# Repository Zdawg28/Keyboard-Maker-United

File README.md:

View this project on [CADLAB.io](https://cadlab.io/project/30098). 

# Keyboard-Maker-United
IEEE Mechanical Keyboard Project Team at Cal Poly Pomona

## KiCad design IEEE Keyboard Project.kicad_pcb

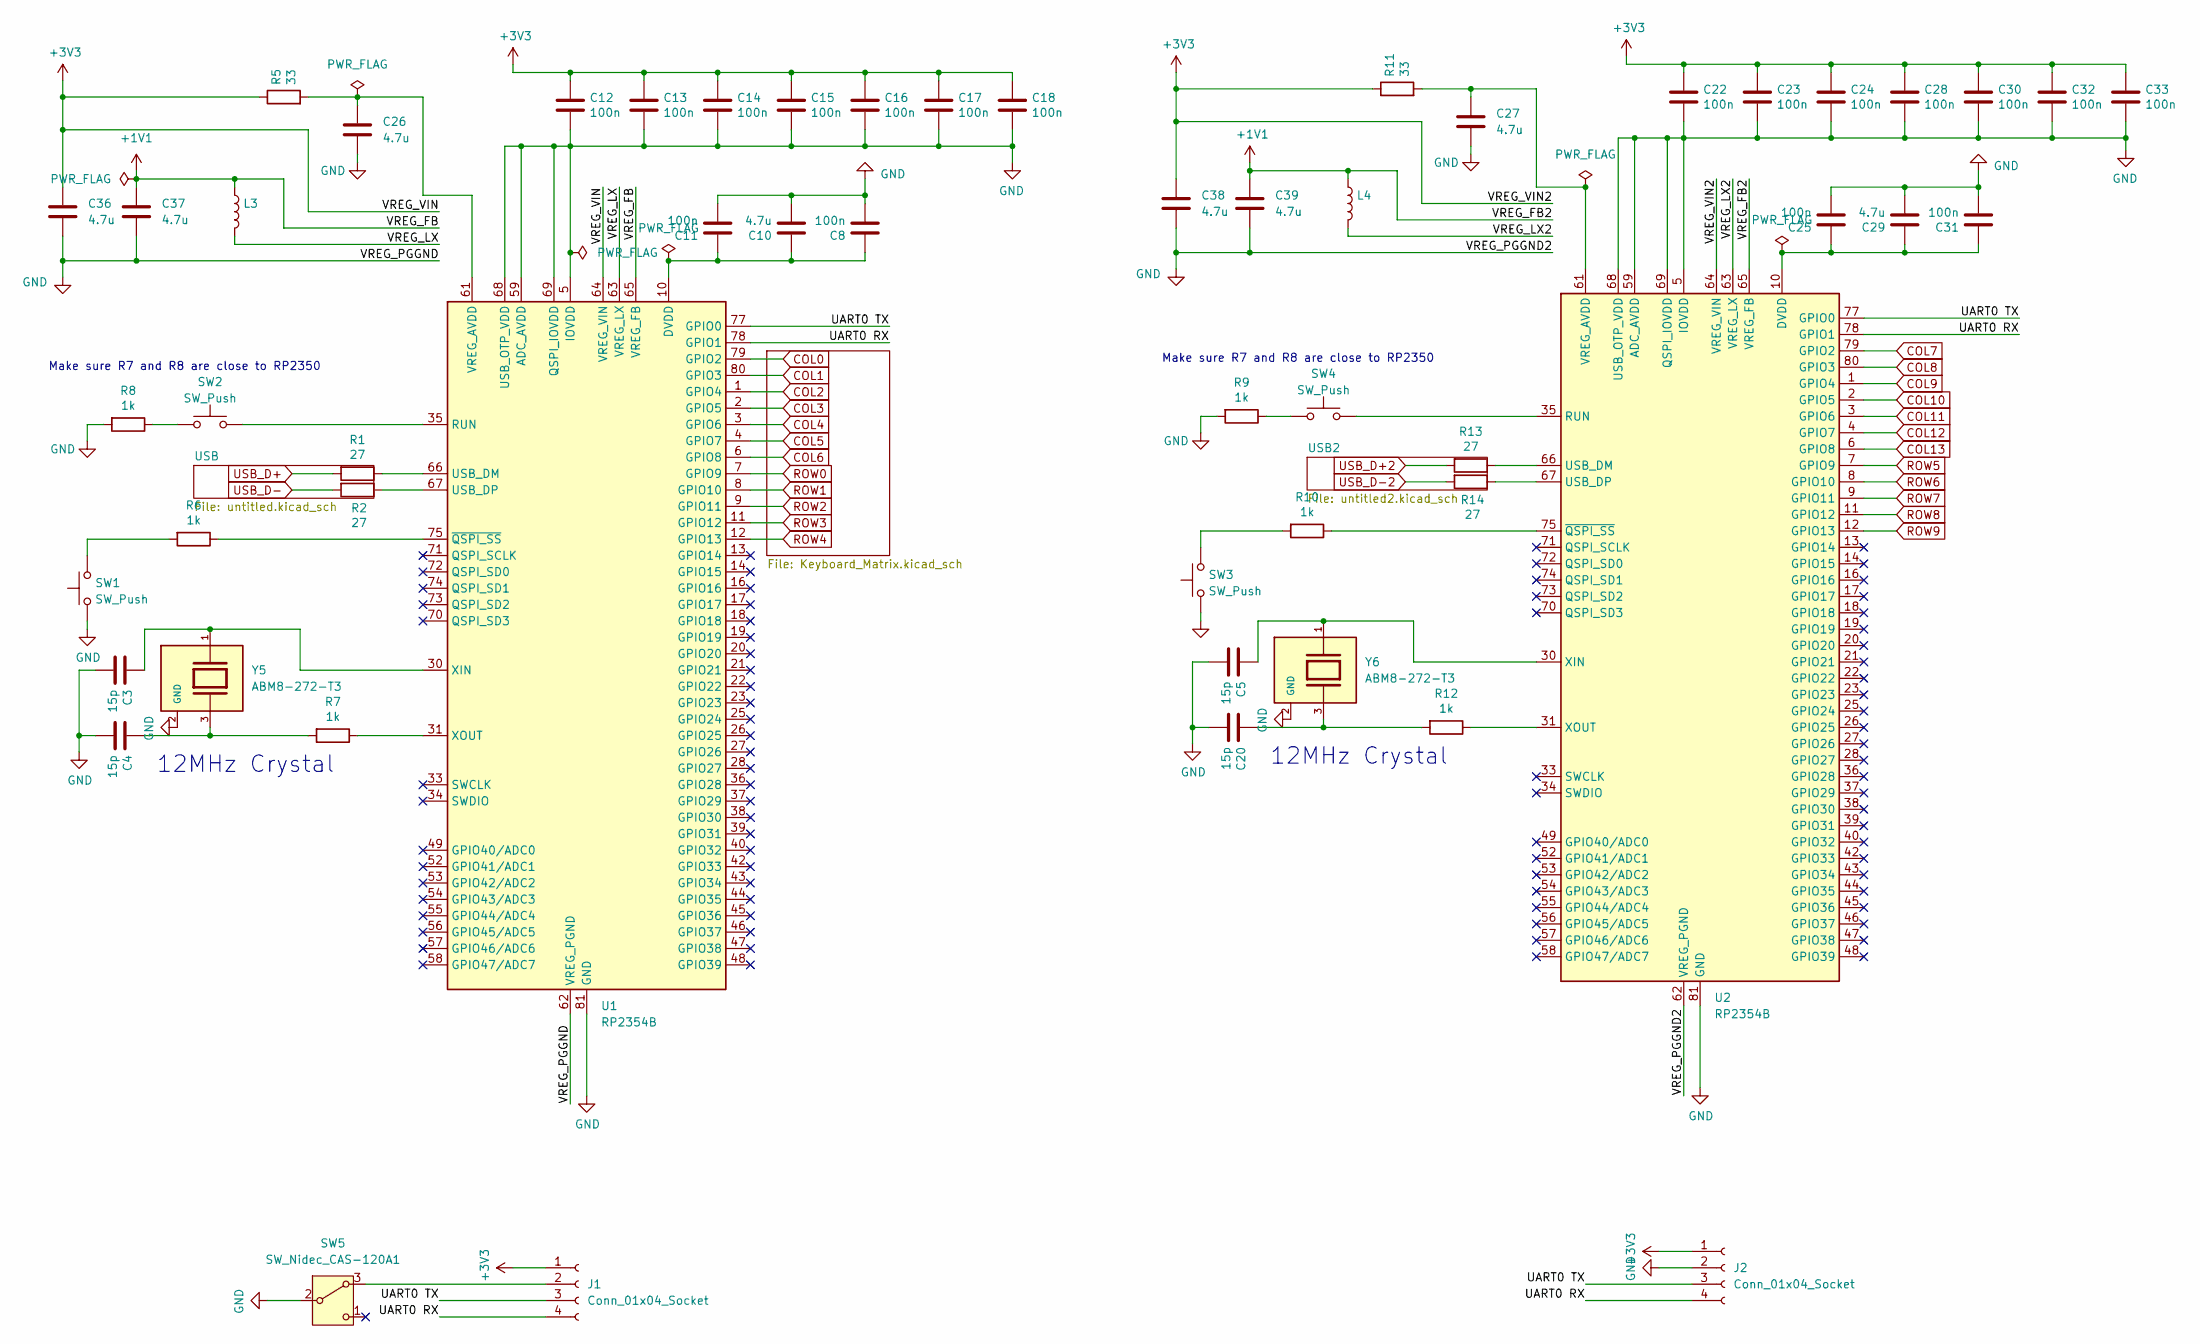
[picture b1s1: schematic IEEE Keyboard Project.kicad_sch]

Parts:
C3, C4, C5, C20: 15p; C_0402_1005Metric
C8, C11, C12, C13, C14, C15, C16, C17, C18, C22, C23, C24, C25, C28, C30, C31, C32, C33: 100n; C_0402_1005Metric
C10, C26, C27, C29, C36, C37, C38, C39: 4.7u; C_0402_1005Metric
J1, J2: Conn_01x04_Socket; JST_EH_S4B-EH_1x04_P2.50mm_Horizontal
L3, L4: 3.3u; L_Coilcraft_LPS3314
R1, R2, R13, R14: 27; R_0402_1005Metric
R5, R11: 33; R_0402_1005Metric
R6, R7, R8, R9, R10, R12: 1k; R_0402_1005Metric
SW1, SW2, SW3, SW4: SW_Push; SW_Push_1P1T_NO_Vertical_Wuerth_434133025816
SW5: SW_Nidec_CAS-120A1; Nidec_Copal_CAS-120A
U1, U2: RP2354B; QFN-80-1EP_10x10mm_P0.4mm_EP3.4x3.4mm
Y5, Y6: ABM8-272-T3; XTAL_ABM8-272-T3; PARTREV 07-29-20

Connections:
+1V1: C37.1, C39.1, L3.1, L4.1, U1.65 (VREG_FB), U2.65 (VREG_FB)
/UART0 RX: J1.4, J2.4, U1.78 (GPIO1), U2.78 (GPIO1)
/UART0 TX: J1.3, J2.3, U1.77 (GPIO0), U2.77 (GPIO0)
/VREG_LX: L3.2, U1.63 (VREG_LX)
/VREG_LX2: L4.2, U2.63 (VREG_LX)
COL0: U1.79 (GPIO2); also elsewhere on the board
COL1: U1.80 (GPIO3); also elsewhere on the board
COL2: U1.1 (GPIO4); also elsewhere on the board
COL3: U1.2 (GPIO5); also elsewhere on the board
COL4: U1.3 (GPIO6); also elsewhere on the board
COL5: U1.4 (GPIO7); also elsewhere on the board
COL6: U1.6 (GPIO8); also elsewhere on the board
COL7: U2.79 (GPIO2); also elsewhere on the board
COL8: U2.80 (GPIO3); also elsewhere on the board
COL12: U2.4 (GPIO7); also elsewhere on the board
COL13: U2.6 (GPIO8); also elsewhere on the board
unnamed: C4.1, R7.2, Y5.3
unnamed: C8.1, C10.1, C11.1, U1.10 (DVDD), U1.32 (DVDD), U1.51 (DVDD)
unnamed 18: C20.1, R12.2, Y6.3; also elsewhere on the board
unnamed: C25.1, C29.1, C31.1, U2.10 (DVDD), U2.32 (DVDD), U2.51 (DVDD)
unnamed: J1.2, SW5.3 (A)
unnamed: R6.2, SW1.2
unnamed: R8.1, SW2.1
unnamed: R9.1, SW4.1
unnamed: R10.2, SW3.2
unnamed: SW2.2, U1.35 (RUN)
unnamed: R1.1, U1.66 (USB_DM)
unnamed: R2.1, U1.67 (USB_DP)
unnamed: C26.1, R5.2, U1.61 (VREG_AVDD)
unnamed: C3.1, U1.30 (XIN), Y5.1
unnamed: R7.1, U1.31 (XOUT)
unnamed: R6.1, U1.75 (~QSPI_SS)
unnamed: SW4.2, U2.35 (RUN)
unnamed: R13.1, U2.66 (USB_DM)
unnamed: R14.1, U2.67 (USB_DP)
unnamed: C27.1, R11.2, U2.61 (VREG_AVDD)
unnamed 97: R12.1, U2.31 (XOUT); also elsewhere on the board
unnamed: R10.1, U2.75 (~QSPI_SS)
ROW0: U1.7 (GPIO9); also elsewhere on the board
ROW1: U1.8 (GPIO10); also elsewhere on the board
ROW2: U1.9 (GPIO11); also elsewhere on the board
ROW3: U1.11 (GPIO12); also elsewhere on the board
ROW4: U1.12 (GPIO13); also elsewhere on the board
ROW5: U2.7 (GPIO9); also elsewhere on the board
ROW6: U2.8 (GPIO10); also elsewhere on the board
ROW7: U2.9 (GPIO11); also elsewhere on the board
ROW8: U2.11 (GPIO12); also elsewhere on the board
ROW9: U2.12 (GPIO13); also elsewhere on the board
USB_D+: R1.2; also elsewhere on the board
USB_D+2: R13.2; also elsewhere on the board
USB_D-: R2.2; also elsewhere on the board
USB_D-2: R14.2; also elsewhere on the board

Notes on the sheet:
Make sure R7 and R8 are close to RP2350
12MHz Crystal

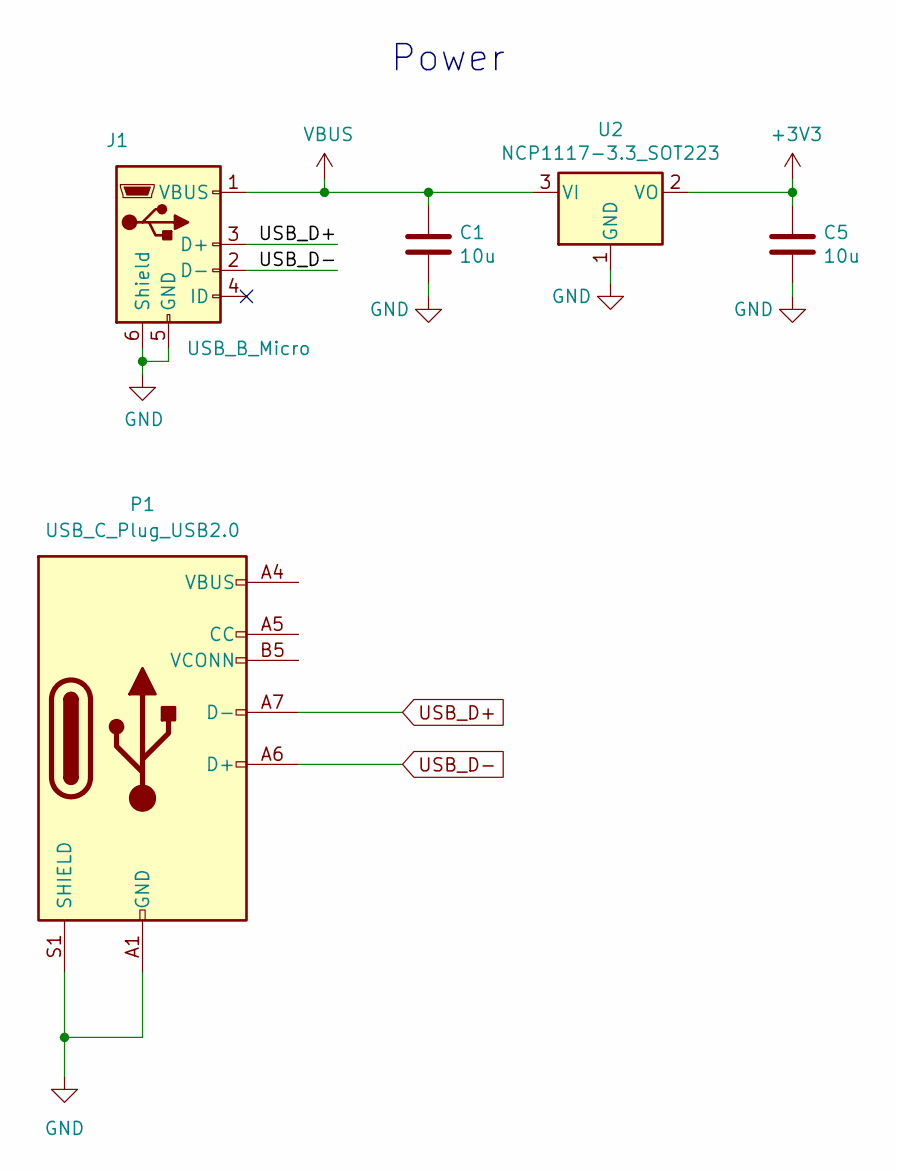
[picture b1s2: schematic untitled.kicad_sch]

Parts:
C1, C5: 10u; C_0805_2012Metric
J1: USB_B_Micro; USB_Micro-B_Amphenol_10103594-0001LF_Horizontal
P1: USB_C_Plug_USB2.0
U2: NCP1117-3.3_SOT223; SOT-223-3_TabPin2

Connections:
/UART0 RX: J1.4; also elsewhere on the board
/UART0 TX: J1.3; also elsewhere on the board
unnamed 76: J1.2; also elsewhere on the board
unnamed: P1.A4 (VBUS), P1.A9 (VBUS), P1.B4 (VBUS), P1.B9 (VBUS)

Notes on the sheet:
Power

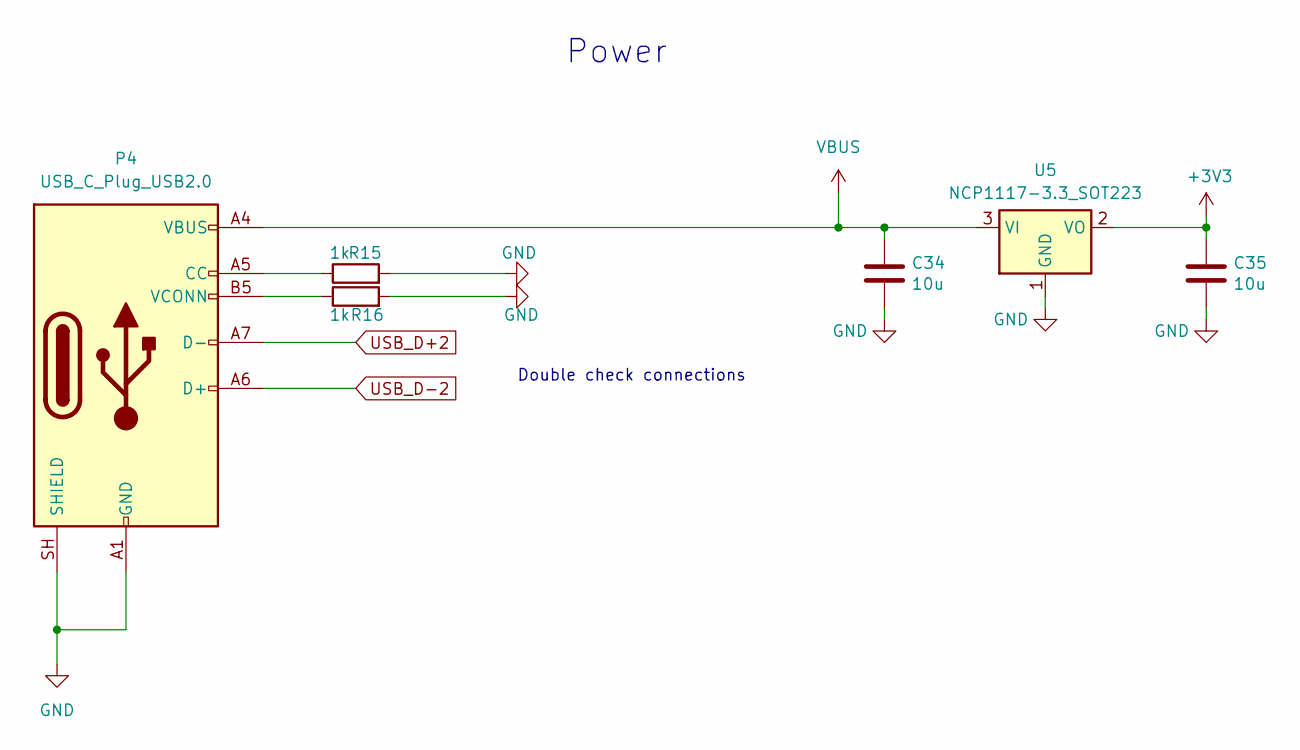
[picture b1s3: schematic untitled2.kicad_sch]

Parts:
C34, C35: 10u; C_0805_2012Metric
P4: USB_C_Plug_USB2.0
R15, R16: 1k; R_0402_1005Metric
U5: NCP1117-3.3_SOT223; SOT-223-3_TabPin2

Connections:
unnamed: P4.A5 (CC), R15.1
unnamed: P4.B5 (VCONN), R16.1
USB_D+2: P4.A7 (D-); also elsewhere on the board
USB_D-2: P4.A6 (D+); also elsewhere on the board
VBUS: C34.1, P4.A4 (VBUS), P4.A9 (VBUS), P4.B4 (VBUS), P4.B9 (VBUS), U5.3 (VI); also elsewhere on the board

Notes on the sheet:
Double check connections
Power

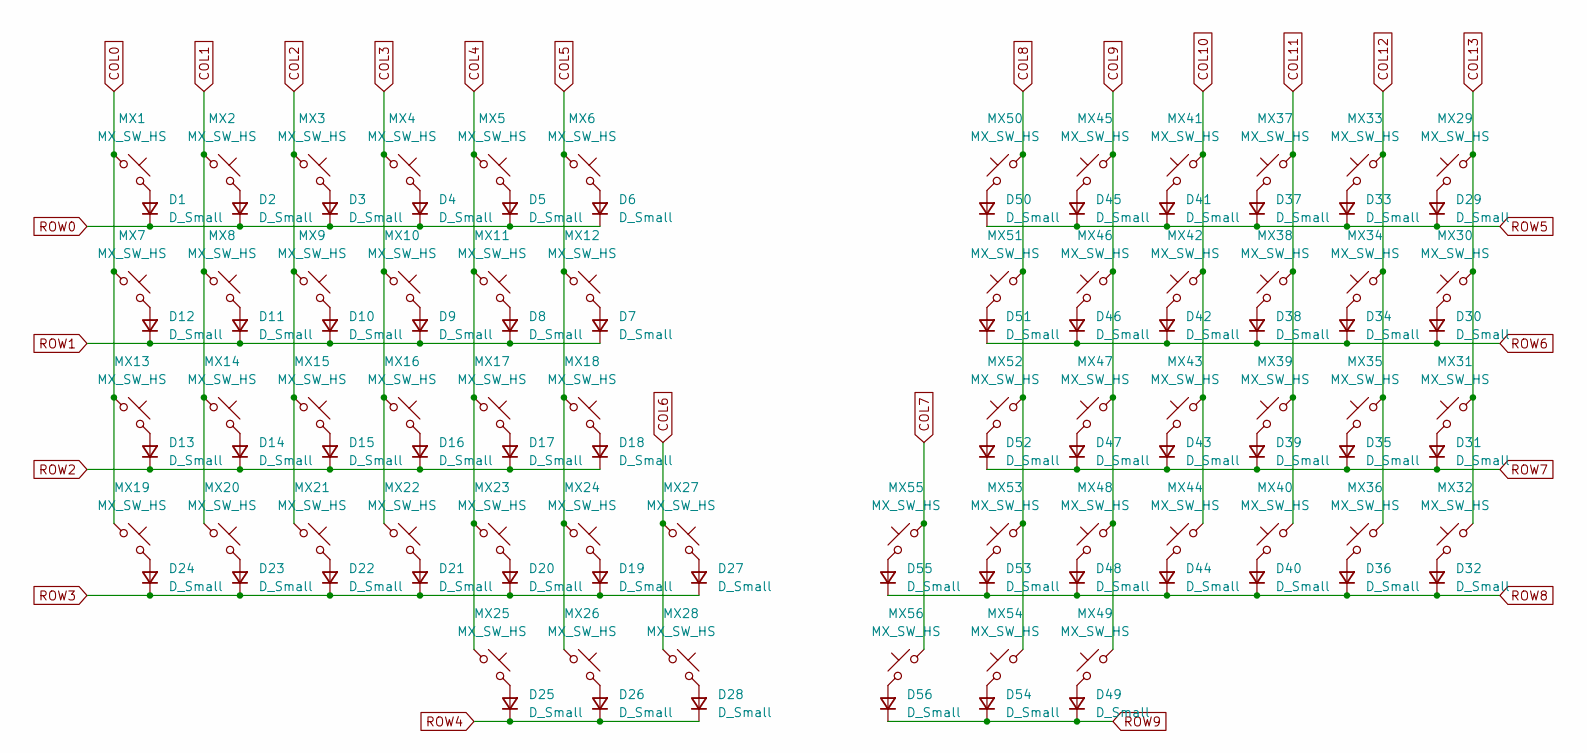
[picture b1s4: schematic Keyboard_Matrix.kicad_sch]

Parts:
D1, D2, D3, D4, D5, D6, D7, D8, D9, D10, D11, D12, D13, D14, D15, D16, D17, D18, D19, D20, D21, D22, D23, D24, D25, D26, D27, D28, D29, D30, D31, D32, D33, D34, D35, D36, D37, D38, D39, D40, D41, D42, D43, D44, D45, D46, D47, D48, D49, D50, D51, D52, D53, D54, D55, D56: D_Small; D_01005_0402Metric
MX1, MX2, MX3, MX4, MX5, MX6, MX7, MX8, MX9, MX10, MX11, MX12, MX13, MX14, MX15, MX16, MX17, MX18, MX19, MX20, MX21, MX22, MX23, MX24, MX25, MX26, MX27, MX28, MX29, MX30, MX31, MX32, MX33, MX34, MX35, MX36, MX37, MX38, MX39, MX40, MX41, MX42, MX43, MX44, MX45, MX46, MX47, MX48, MX49, MX50, MX51, MX52, MX53, MX54, MX55, MX56: MX_SW_HS; SW_Cherry_MX_1.00u_PCB

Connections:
COL0: MX1.1, MX7.1, MX13.1, MX19.1; also elsewhere on the board
COL1: MX2.1, MX8.1, MX14.1, MX20.1; also elsewhere on the board
COL2: MX3.1, MX9.1, MX15.1, MX21.1; also elsewhere on the board
COL3: MX4.1, MX10.1, MX16.1, MX22.1; also elsewhere on the board
COL4: MX5.1, MX11.1, MX17.1, MX23.1, MX25.1; also elsewhere on the board
COL5: MX6.1, MX12.1, MX18.1, MX24.1, MX26.1; also elsewhere on the board
COL6: MX27.1, MX28.1; also elsewhere on the board
COL7: MX55.1, MX56.1; also elsewhere on the board
COL8: MX50.1, MX51.1, MX52.1, MX53.1, MX54.1; also elsewhere on the board
COL12: MX33.1, MX34.1, MX35.1, MX36.1; also elsewhere on the board
COL13: MX29.1, MX30.1, MX31.1, MX32.1; also elsewhere on the board
unnamed: D1.2 (A), MX1.2
unnamed: D2.2 (A), MX2.2
unnamed: D3.2 (A), MX3.2
unnamed: D4.2 (A), MX4.2
unnamed: D5.2 (A), MX5.2
unnamed: D6.2 (A), MX6.2
unnamed: D7.2 (A), MX12.2
unnamed: D8.2 (A), MX11.2
unnamed: D9.2 (A), MX10.2
unnamed: D10.2 (A), MX9.2
unnamed: D11.2 (A), MX8.2
unnamed: D12.2 (A), MX7.2
unnamed: D13.2 (A), MX13.2
unnamed: D14.2 (A), MX14.2
unnamed: D15.2 (A), MX15.2
unnamed: D16.2 (A), MX16.2
unnamed: D17.2 (A), MX17.2
unnamed: D18.2 (A), MX18.2
unnamed: D19.2 (A), MX24.2
unnamed: D20.2 (A), MX23.2
unnamed: D21.2 (A), MX22.2
unnamed: D22.2 (A), MX21.2
unnamed: D23.2 (A), MX20.2
unnamed: D24.2 (A), MX19.2
unnamed: D25.2 (A), MX25.2
unnamed: D26.2 (A), MX26.2
unnamed: D27.2 (A), MX27.2
unnamed: D28.2 (A), MX28.2
unnamed: D29.2 (A), MX29.2
unnamed: D30.2 (A), MX30.2
unnamed: D31.2 (A), MX31.2
unnamed: D32.2 (A), MX32.2
unnamed: D33.2 (A), MX33.2
unnamed: D34.2 (A), MX34.2
unnamed: D35.2 (A), MX35.2
unnamed: D36.2 (A), MX36.2
unnamed: D37.2 (A), MX37.2
unnamed: D38.2 (A), MX38.2
unnamed: D39.2 (A), MX39.2
unnamed: D40.2 (A), MX40.2
unnamed: D41.2 (A), MX41.2
unnamed: D42.2 (A), MX42.2
unnamed: D43.2 (A), MX43.2
unnamed: D44.2 (A), MX44.2
unnamed: D45.2 (A), MX45.2
unnamed: D46.2 (A), MX46.2
unnamed: D47.2 (A), MX47.2
unnamed: D48.2 (A), MX48.2
unnamed: D49.2 (A), MX49.2
unnamed: D50.2 (A), MX50.2
unnamed: D51.2 (A), MX51.2
unnamed: D52.2 (A), MX52.2
unnamed: D53.2 (A), MX53.2
unnamed: D54.2 (A), MX54.2
unnamed: D55.2 (A), MX55.2
unnamed: D56.2 (A), MX56.2
ROW0: D1.1 (K), D2.1 (K), D3.1 (K), D4.1 (K), D5.1 (K), D6.1 (K); also elsewhere on the board
ROW1: D7.1 (K), D8.1 (K), D9.1 (K), D10.1 (K), D11.1 (K), D12.1 (K); also elsewhere on the board
ROW2: D13.1 (K), D14.1 (K), D15.1 (K), D16.1 (K), D17.1 (K), D18.1 (K); also elsewhere on the board
ROW3: D19.1 (K), D20.1 (K), D21.1 (K), D22.1 (K), D23.1 (K), D24.1 (K), D27.1 (K); also elsewhere on the board
ROW4: D25.1 (K), D26.1 (K), D28.1 (K); also elsewhere on the board
ROW5: D29.1 (K), D33.1 (K), D37.1 (K), D41.1 (K), D45.1 (K), D50.1 (K); also elsewhere on the board
ROW6: D30.1 (K), D34.1 (K), D38.1 (K), D42.1 (K), D46.1 (K), D51.1 (K); also elsewhere on the board
ROW7: D31.1 (K), D35.1 (K), D39.1 (K), D43.1 (K), D47.1 (K), D52.1 (K); also elsewhere on the board
ROW8: D32.1 (K), D36.1 (K), D40.1 (K), D44.1 (K), D48.1 (K), D53.1 (K), D55.1 (K); also elsewhere on the board
ROW9: D49.1 (K), D54.1 (K), D56.1 (K); also elsewhere on the board

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
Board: 4 copper layers, 183 parts (55 on the bottom side), 119 nets, no tracks yet.

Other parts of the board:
C2, C6: 10u; C_0805_2012Metric
C5#2, C20#2: 15p; C_0402_1005Metric
P3: USB_C_Plug_USB2.0; TE_2340901-1
R3, R4, R12#2: 1k; R_0402_1005Metric
U4: NCP1117-3.3_SOT223; SOT-223-3_TabPin2
Y2: ABM8-272-T3; Crystal_SMD_3225-4Pin_3.2x2.5mm

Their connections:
unnamed 18: C20#2.1, R12#2.2, Y2.3; also elsewhere on the board
unnamed: P3.A5 (CC), R3.1
unnamed: P3.B5 (VCONN), R4.1
unnamed 97: R12#2.1; also elsewhere on the board
USB_D+: P3.A7 (D-); also elsewhere on the board
USB_D-: P3.A6 (D+); also elsewhere on the board
VBUS: C2.1, U4.3 (VI); also elsewhere on the board

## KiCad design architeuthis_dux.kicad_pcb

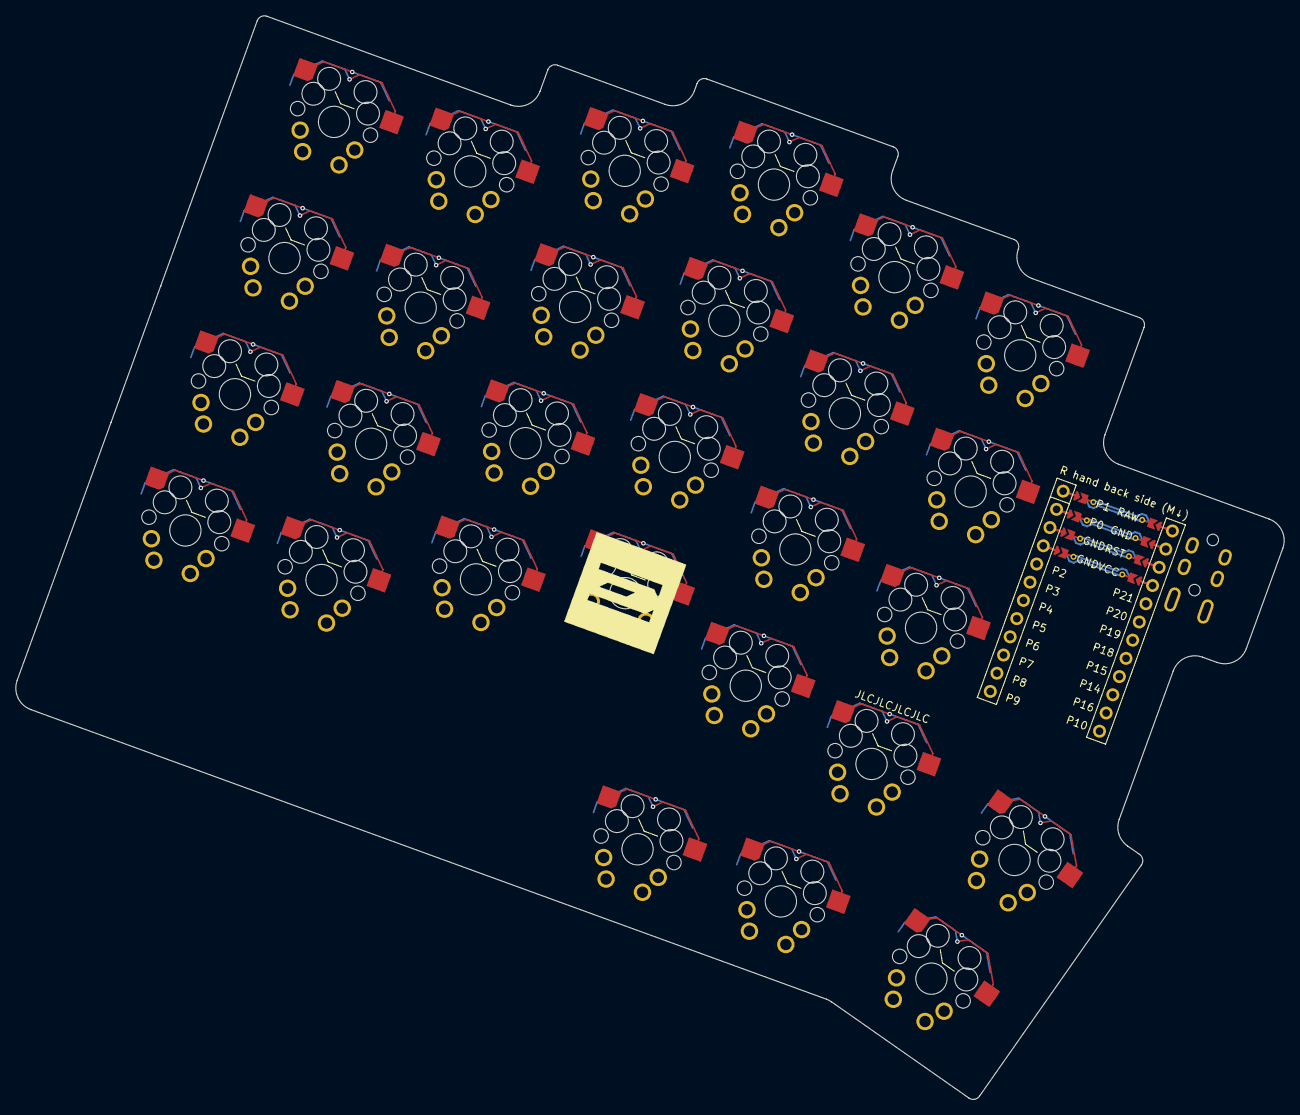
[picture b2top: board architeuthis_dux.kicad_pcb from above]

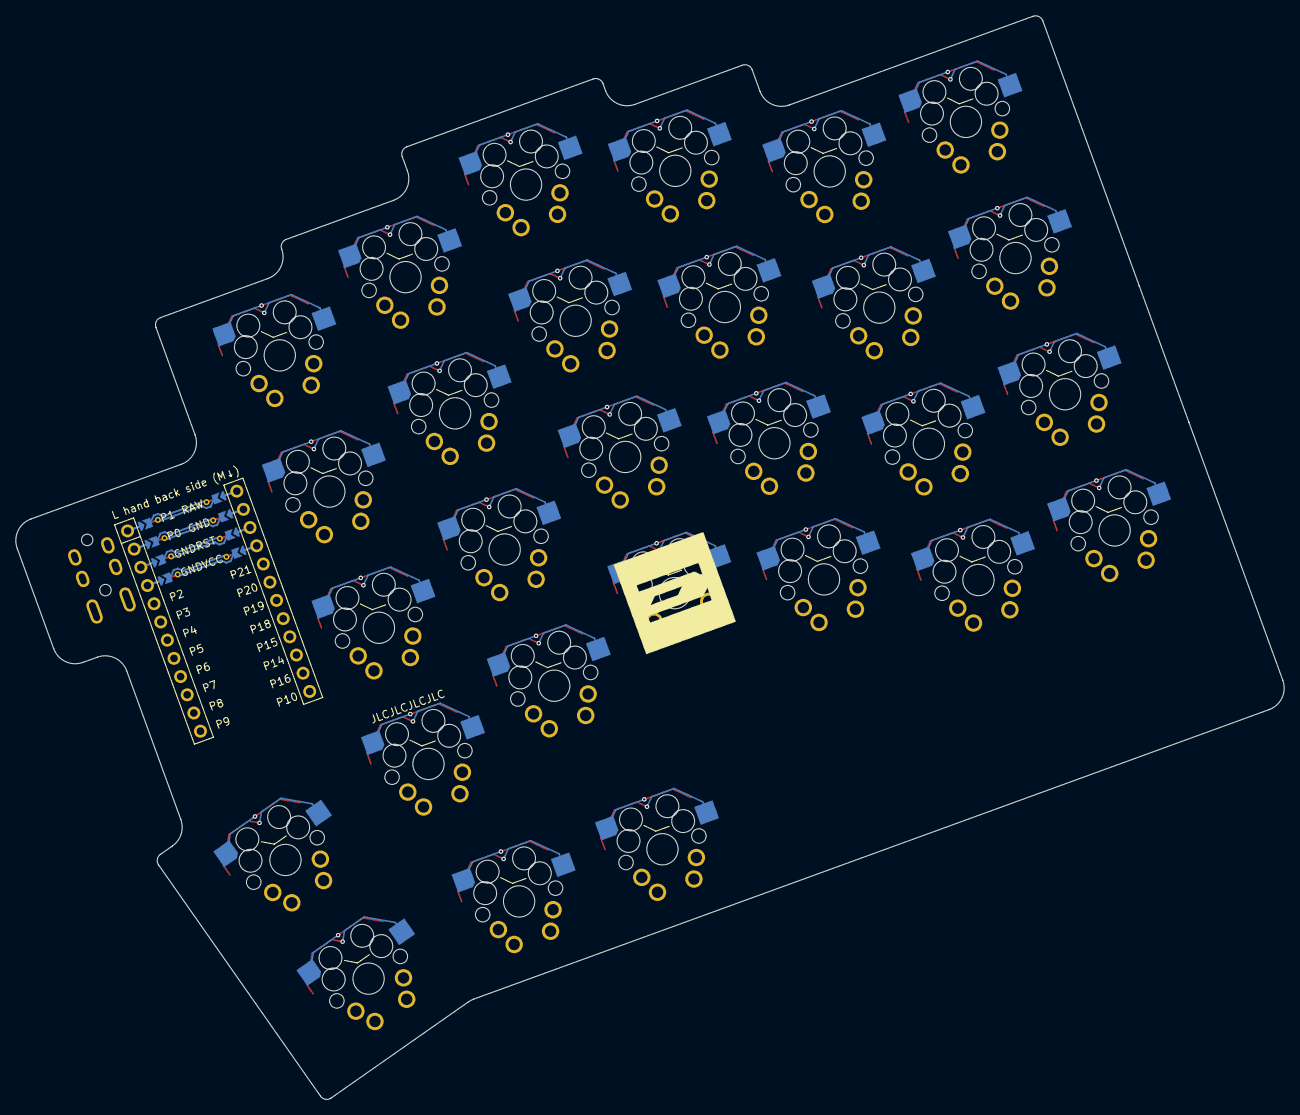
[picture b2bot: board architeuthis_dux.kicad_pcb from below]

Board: 2 copper layers, 166.3 x 142.1 mm, 31 parts (28 on the bottom side), 4 nets.

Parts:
LOGO1: utility_ergogen_logo
MCU1: mcu_nice_nano
S1, S2, S3, S4, S5, S6, S7, S8, S9, S10, S11, S12, S13, S14, S15, S16, S17, S18, S19, S20, S21, S22, S23, S24, S25, S26, S27, S28: switch_mx
TRRS1: trrs_pj320a (reversible, symmetric)

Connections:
=column_net: S1.1, S2.1, S3.1, S4.1, S5.1, S6.1, S7.1, S8.1, S9.1, S10.1, S11.1, S12.1, S13.1, S14.1, S15.1, S16.1, S17.1, S18.1, S19.1, S20.1, S21.1, S22.1, S23.1, S24.1, S25.1, S26.1, S27.1, S28.1
GND: MCU1.102, MCU1.121, MCU1.122, S1.2, S2.2, S3.2, S4.2, S5.2, S6.2, S7.2, S8.2, S9.2, S10.2, S11.2, S12.2, S13.2, S14.2, S15.2, S16.2, S17.2, S18.2, S19.2, S20.2, S21.2, S22.2, S23.2, S24.2, S25.2, S26.2, S27.2, S28.2, TRRS1.2
P2: MCU1.20, TRRS1.3
VCC: MCU1.104, TRRS1.4

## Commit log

2026-02-13 Add files via upload
    Keyboard Kicad Project
2026-02-20 Backlink to CADLAB.io has been added.
2026-03-06 Add files via upload
    Latest Ergogen design
2026-03-26 Most updated Kicad design
2026-03-31 usb update
2026-04-02 Finalized schematic and most updated PCB Layout
2026-04-02 Add files via upload
    PCB design as of april first
2026-04-02 Sorting out components on PCB
